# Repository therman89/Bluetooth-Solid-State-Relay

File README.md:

# Bluetooth-Solid-State-Relay
Bluetooth controlled SSR with isolated gate driver. Radio module is either BGM111 or MGM111

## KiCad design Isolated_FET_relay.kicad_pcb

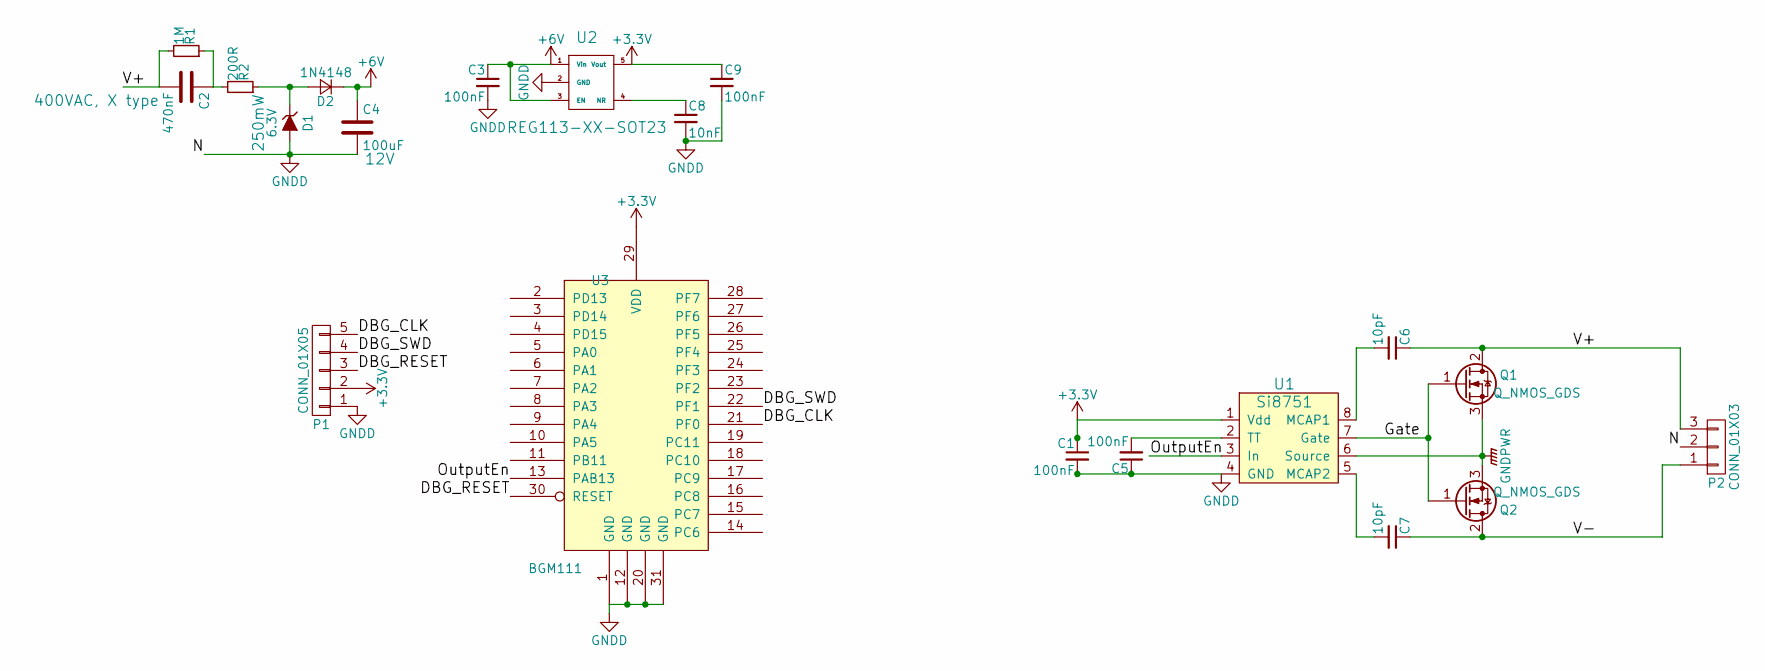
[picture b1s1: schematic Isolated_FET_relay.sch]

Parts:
C1, C3, C5, C9: 100nF; C_0603
C2: 470nF; C_Rect_L18.0mm_W7.0mm_P15.00mm_FKS3_FKP3
C4: 100uF; CP_Radial_D8.0mm_P3.50mm; Voltage 12V
C6, C7: 10pF; C_0603
C8: 10nF; C_0603
D1: 6.3V; D_SOD-123
D2: 1N4148; D_SOD-123
P1: CONN_01X05; Pin_Header_Straight_1x05_Pitch2.00mm
P2: CONN_01X03; AK300-3
Q1, Q2: Q_NMOS_GDS; TO-220_Neutral123_Vertical
R1: 1M; R_0603_HandSoldering
R2: 200R; R_0603_HandSoldering
U1: Si8751; SOIC-8_3.9x4.9mm_Pitch1.27mm
U2: REG113-XX-SOT23; SOT-23-5
U3: BGM111

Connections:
+3V3: C1.1, C9.1, P1.2, U1.1 (Vdd), U2.5 (Vout), U3.29 (VDD)
+6V: C3.1, C4.1, D2.1 (K), U2.1 (Vin), U2.3 (EN)
/DBG_CLK: P1.5, U3.21 (PF0)
/DBG_RESET: P1.3, U3.30 (RESET)
/DBG_SWD: P1.4, U3.22 (PF1)
/Gate: Q1.1 (G), Q2.1 (G), U1.7 (Gate)
/OutputEn: U1.3 (In), U3.13 (PAB13)
/V+: C2.2, C6.1, P2.3, Q1.2 (D), R1.2
/V-: C7.1, P2.1, Q2.2 (D)
GNDD: C1.2, C3.2, C4.2, C5.1, C8.2, C9.2, D1.2 (A), P1.1, P2.2, U1.4 (GND), U2.2 (GND), U3.1 (GND), U3.12 (GND), U3.20 (GND), U3.31 (GND)
GNDPWR: Q1.3 (S), Q2.3 (S), U1.6 (Source)
unnamed: C2.1, R1.1, R2.2
unnamed: C5.2, U1.2 (TT)
unnamed: C6.2, U1.8 (MCAP1)
unnamed: C7.2, U1.5 (MCAP2)
unnamed: C8.1, U2.4 (NR)
unnamed: D1.1 (K), D2.2 (A), R2.1

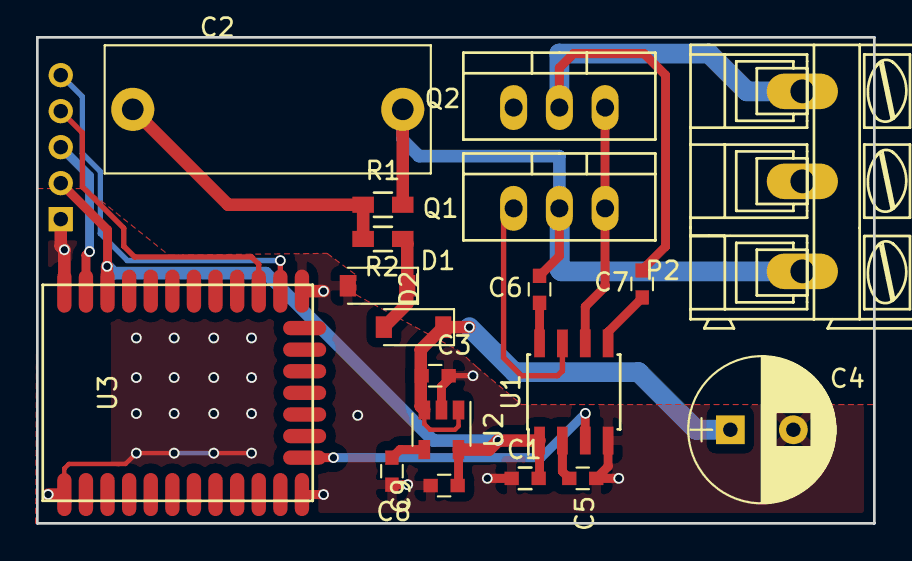
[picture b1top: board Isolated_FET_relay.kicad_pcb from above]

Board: 2 copper layers, 46.5 x 27.0 mm, 20 parts (1 on the bottom side), 17 nets.

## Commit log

2017-01-26 Creating repository
2017-01-27 Added gitignore. Created new layout to fit in the box
2017-01-27 removed bak file
2017-01-27 Created new layout concept
